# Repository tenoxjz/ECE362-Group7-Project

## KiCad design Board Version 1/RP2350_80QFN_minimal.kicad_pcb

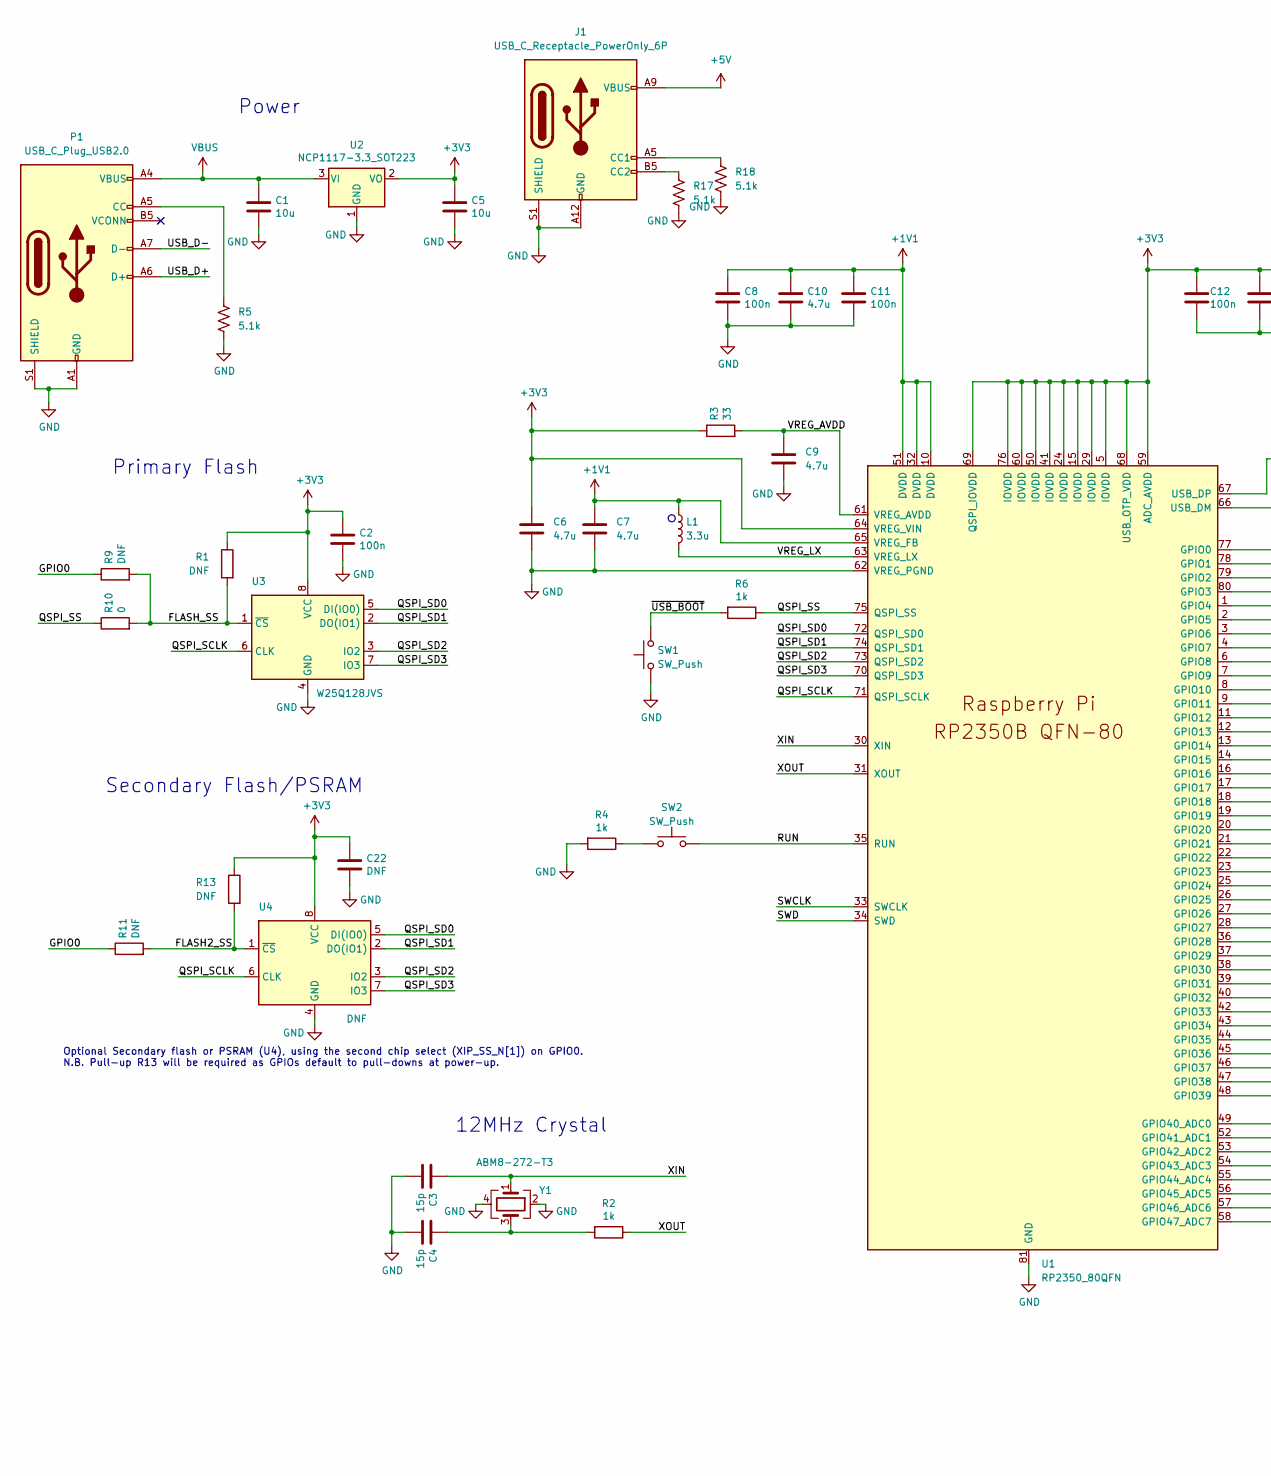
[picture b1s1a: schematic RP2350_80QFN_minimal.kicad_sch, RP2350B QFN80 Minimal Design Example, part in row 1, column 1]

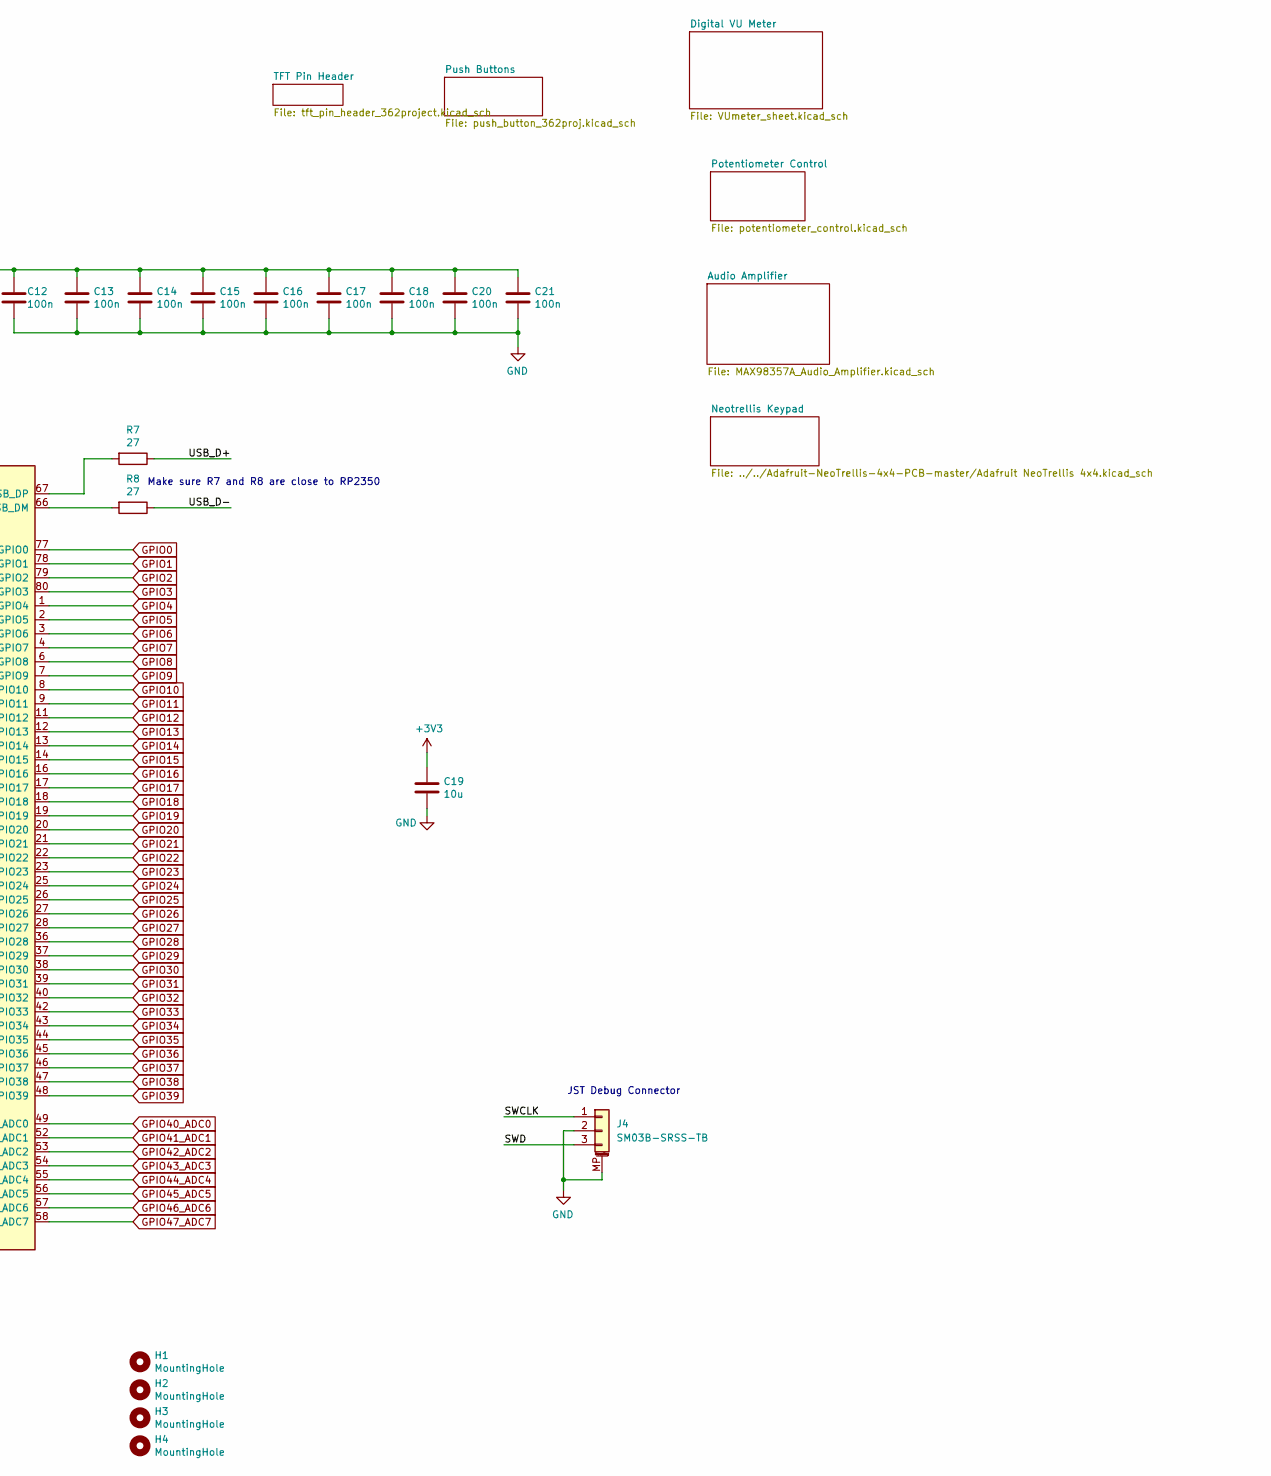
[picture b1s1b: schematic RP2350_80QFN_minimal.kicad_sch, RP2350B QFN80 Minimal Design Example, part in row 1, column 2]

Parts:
C1, C5, C19: 10u; C_0805_2012Metric
C2, C8, C11, C12, C13, C14, C15, C16, C17, C18, C20, C21: 100n; C_0402_1005Metric
C3, C4: 15p; C_0402_1005Metric
C6, C7: 4.7u; C_0402_1005Metric_small_pads
C9, C10: 4.7u; C_0402_1005Metric
C22: DNF; C_0402_1005Metric
H1, H2, H3, H4: MountingHole; MountingHole_2.7mm_M2.5
J1: USB_C_Receptacle_PowerOnly_6P; USB_C_Receptacle_GCT_USB4125-xx-x-0190_6P_TopMnt_Horizontal
J4: SM03B-SRSS-TB; JST_SH_SM03B-SRSS-TB_1x03-1MP_P1.00mm_Horizontal
L1: 3.3u; L_pol_2016
P1: USB_C_Plug_USB2.0; USB_C_Receptacle_HRO_TYPE-C-31-M-12
R1, R9, R11, R13: DNF; R_0402_1005Metric
R2, R4, R6: 1k; R_0402_1005Metric
R3: 33; R_0402_1005Metric
R5, R17, R18: 5.1k; R_0603_1608Metric
R7, R8: 27; R_0402_1005Metric
R10: 0; R_0402_1005Metric
SW1, SW2: SW_Push; SW_Push_1P1T_NO_Vertical_Wuerth_434133025816
U1: RP2350_80QFN; RP2350-QFN-80-1EP_10x10_P0.4mm_EP3.4x3.4mm_ThermalVias
U2: NCP1117-3.3_SOT223; SOT-223-3_TabPin2
U3: W25Q128JVS; SOIC-8_5.23x5.23mm_P1.27mm
U4: DNF; SOIC-8_5.23x5.23mm_P1.27mm
Y1: ABM8-272-T3; Crystal_SMD_3225-4Pin_3.2x2.5mm

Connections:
+1V1: C7.1, C8.1, C10.1, C11.1, L1.1, U1.10 (DVDD), U1.32 (DVDD), U1.51 (DVDD), U1.65 (VREG_FB)
+5V: J1.A9 (VBUS), J1.B9 (VBUS); also elsewhere on the board
/FLASH2_SS: R11.2, R13.2, U4.1 (~CS)
/FLASH_SS: R1.2, R9.2, R10.2, U3.1 (~CS)
/QSPI_SCLK: U1.71 (QSPI_SCLK), U3.6 (CLK), U4.6 (CLK)
/QSPI_SD0: U1.72 (QSPI_SD0), U3.5 (DI(IO0)), U4.5 (DI(IO0))
/QSPI_SD1: U1.74 (QSPI_SD1), U3.2 (DO(IO1)), U4.2 (DO(IO1))
/QSPI_SD2: U1.73 (QSPI_SD2), U3.3 (IO2), U4.3 (IO2)
/QSPI_SD3: U1.70 (QSPI_SD3), U3.7 (IO3), U4.7 (IO3)
/QSPI_SS: R6.1, R10.1, U1.75 (QSPI_SS)
/RUN: SW2.2, U1.35 (RUN)
/SWCLK: J4.1, U1.33 (SWCLK)
/SWD: J4.3, U1.34 (SWD)
/USB_D+: P1.A6 (D+), R7.1
/USB_D-: P1.A7 (D-), R8.1
/VREG_AVDD: C9.1, R3.2, U1.61 (VREG_AVDD)
/VREG_LX: L1.2, U1.63 (VREG_LX)
/XIN: C3.1, U1.30 (XIN), Y1.1
/XOUT: R2.1, U1.31 (XOUT)
/~USB_BOOT: R6.2, SW1.2
GND: C1.2, C2.2, C3.2, C4.2, C5.2, C6.2, C7.2, C8.2, C9.2, C10.2, C11.2, C12.2, C13.2, C14.2, C15.2, C16.2, C17.2, C18.2, C19.2, C20.2, C21.2, C22.2, J1.A12 (GND), J1.B12 (GND), J1.S1 (SHIELD), J4.2, J4.MP (MountPin), P1.A1 (GND), P1.A12 (GND), P1.B1 (GND), P1.B12 (GND), P1.S1 (SHIELD), R4.2, R5.2, R17.2, R18.2, SW1.1, U1.62 (VREG_PGND), U1.81 (GND), U2.1 (GND), U3.4 (GND), U4.4 (GND), Y1.2, Y1.4; also elsewhere on the board
GPIO0: R9.1, R11.1, U1.77 (GPIO0)
GPIO1: U1.78 (GPIO1)
GPIO2: U1.79 (GPIO2)
GPIO3: U1.80 (GPIO3); also elsewhere on the board
GPIO4: U1.1 (GPIO4); also elsewhere on the board
GPIO5: U1.2 (GPIO5); also elsewhere on the board
GPIO6: U1.3 (GPIO6); also elsewhere on the board
GPIO7: U1.4 (GPIO7); also elsewhere on the board
GPIO8: U1.6 (GPIO8)
GPIO9: U1.7 (GPIO9)
GPIO10: U1.8 (GPIO10)
GPIO11: U1.9 (GPIO11)
GPIO12: U1.11 (GPIO12)
GPIO13: U1.12 (GPIO13)
GPIO14: U1.13 (GPIO14)
GPIO15: U1.14 (GPIO15)
GPIO16: U1.16 (GPIO16); also elsewhere on the board
GPIO17: U1.17 (GPIO17); also elsewhere on the board
GPIO18: U1.18 (GPIO18); also elsewhere on the board
GPIO19: U1.19 (GPIO19); also elsewhere on the board
GPIO20: U1.20 (GPIO20); also elsewhere on the board
GPIO21: U1.21 (GPIO21)
GPIO22: U1.22 (GPIO22)
GPIO23: U1.23 (GPIO23)
GPIO24: U1.25 (GPIO24); also elsewhere on the board
GPIO25: U1.26 (GPIO25); also elsewhere on the board
GPIO26: U1.27 (GPIO26)
GPIO27: U1.28 (GPIO27)
GPIO28: U1.36 (GPIO28)
GPIO29: U1.37 (GPIO29); also elsewhere on the board
GPIO30: U1.38 (GPIO30); also elsewhere on the board
GPIO31: U1.39 (GPIO31); also elsewhere on the board
GPIO32: U1.40 (GPIO32)
GPIO33: U1.42 (GPIO33)
GPIO34: U1.43 (GPIO34)
GPIO35: U1.44 (GPIO35)
GPIO36: U1.45 (GPIO36); also elsewhere on the board
GPIO37: U1.46 (GPIO37); also elsewhere on the board
GPIO38: U1.47 (GPIO38); also elsewhere on the board
GPIO39: U1.48 (GPIO39); also elsewhere on the board
GPIO40_ADC0: U1.49 (GPIO40_ADC0)
GPIO41_ADC1: U1.52 (GPIO41_ADC1)
GPIO42_ADC2: U1.53 (GPIO42_ADC2)
GPIO43_ADC3: U1.54 (GPIO43_ADC3); also elsewhere on the board
GPIO44_ADC4: U1.55 (GPIO44_ADC4)
GPIO45_ADC5: U1.56 (GPIO45_ADC5); also elsewhere on the board
GPIO46_ADC6: U1.57 (GPIO46_ADC6)
GPIO47_ADC7: U1.58 (GPIO47_ADC7); also elsewhere on the board
unnamed: C4.1, R2.2, Y1.3
unnamed: J1.A5 (CC1), R18.1
unnamed: J1.B5 (CC2), R17.1
unnamed: P1.A5 (CC), R5.1
unnamed: R4.1, SW2.1
unnamed: R8.2, U1.66 (USB_DM)
unnamed: R7.2, U1.67 (USB_DP)
VBUS: C1.1, P1.A4 (VBUS), P1.A9 (VBUS), P1.B4 (VBUS), P1.B9 (VBUS), U2.3 (VI)

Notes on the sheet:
Optional Secondary flash or PSRAM (U4), using the second chip select (XIP_SS_N[1]) on GPIO0. N.B. Pull-up R13 will be required as GPIOs default to pull-downs at power-up.
12MHz Crystal
Primary Flash
JST Debug Connector
Make sure R7 and R8 are close to RP2350
Secondary Flash/PSRAM
Power

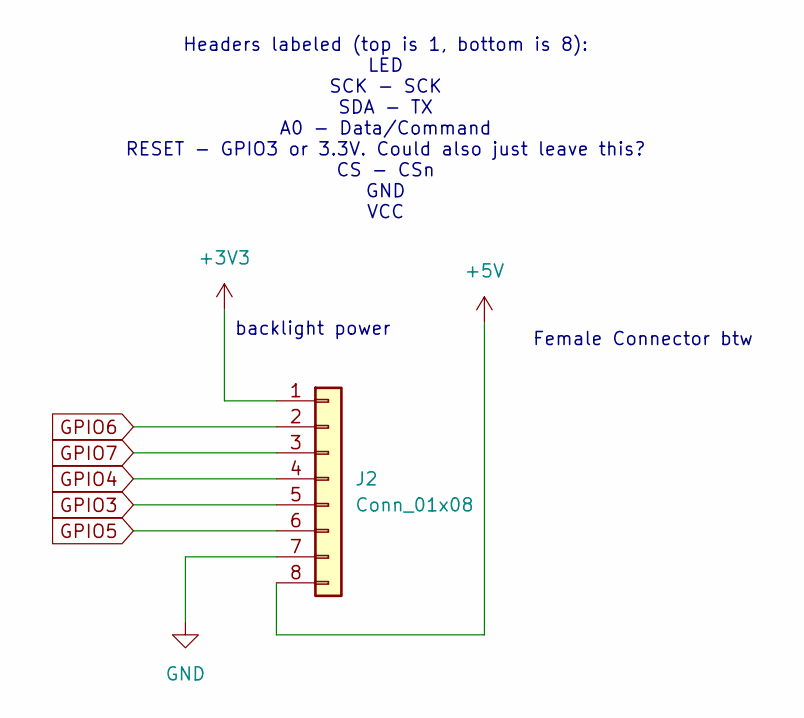
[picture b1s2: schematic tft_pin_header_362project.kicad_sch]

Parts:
J2: Conn_01x08; PinHeader_1x08_P2.54mm_Vertical

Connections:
+5V: J2.8; also elsewhere on the board
GND: J2.7; also elsewhere on the board
GPIO3: J2.5; also elsewhere on the board
GPIO4: J2.4; also elsewhere on the board
GPIO5: J2.6; also elsewhere on the board
GPIO6: J2.2; also elsewhere on the board
GPIO7: J2.3; also elsewhere on the board

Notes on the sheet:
Headers labeled (top is 1, bottom is 8): LED SCK - SCK SDA - TX A0 - Data/Command RESET - GPIO3 or 3.3V. Could also just leave this? CS - CSn GND VCC
backlight power
Female Connector btw

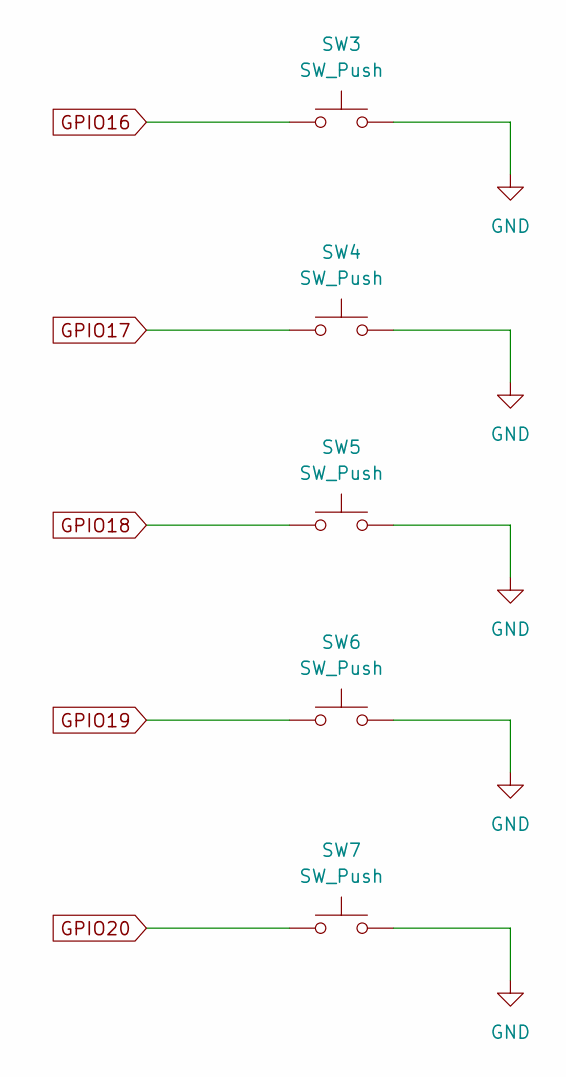
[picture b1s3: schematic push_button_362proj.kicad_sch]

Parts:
SW3, SW4, SW5, SW6, SW7: SW_Push; SW_Push_1P1T_NO_Vertical_Wuerth_434133025816

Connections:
GND: SW3.2, SW4.2, SW5.2, SW6.2, SW7.2; also elsewhere on the board
GPIO16: SW3.1; also elsewhere on the board
GPIO17: SW4.1; also elsewhere on the board
GPIO18: SW5.1; also elsewhere on the board
GPIO19: SW6.1; also elsewhere on the board
GPIO20: SW7.1; also elsewhere on the board

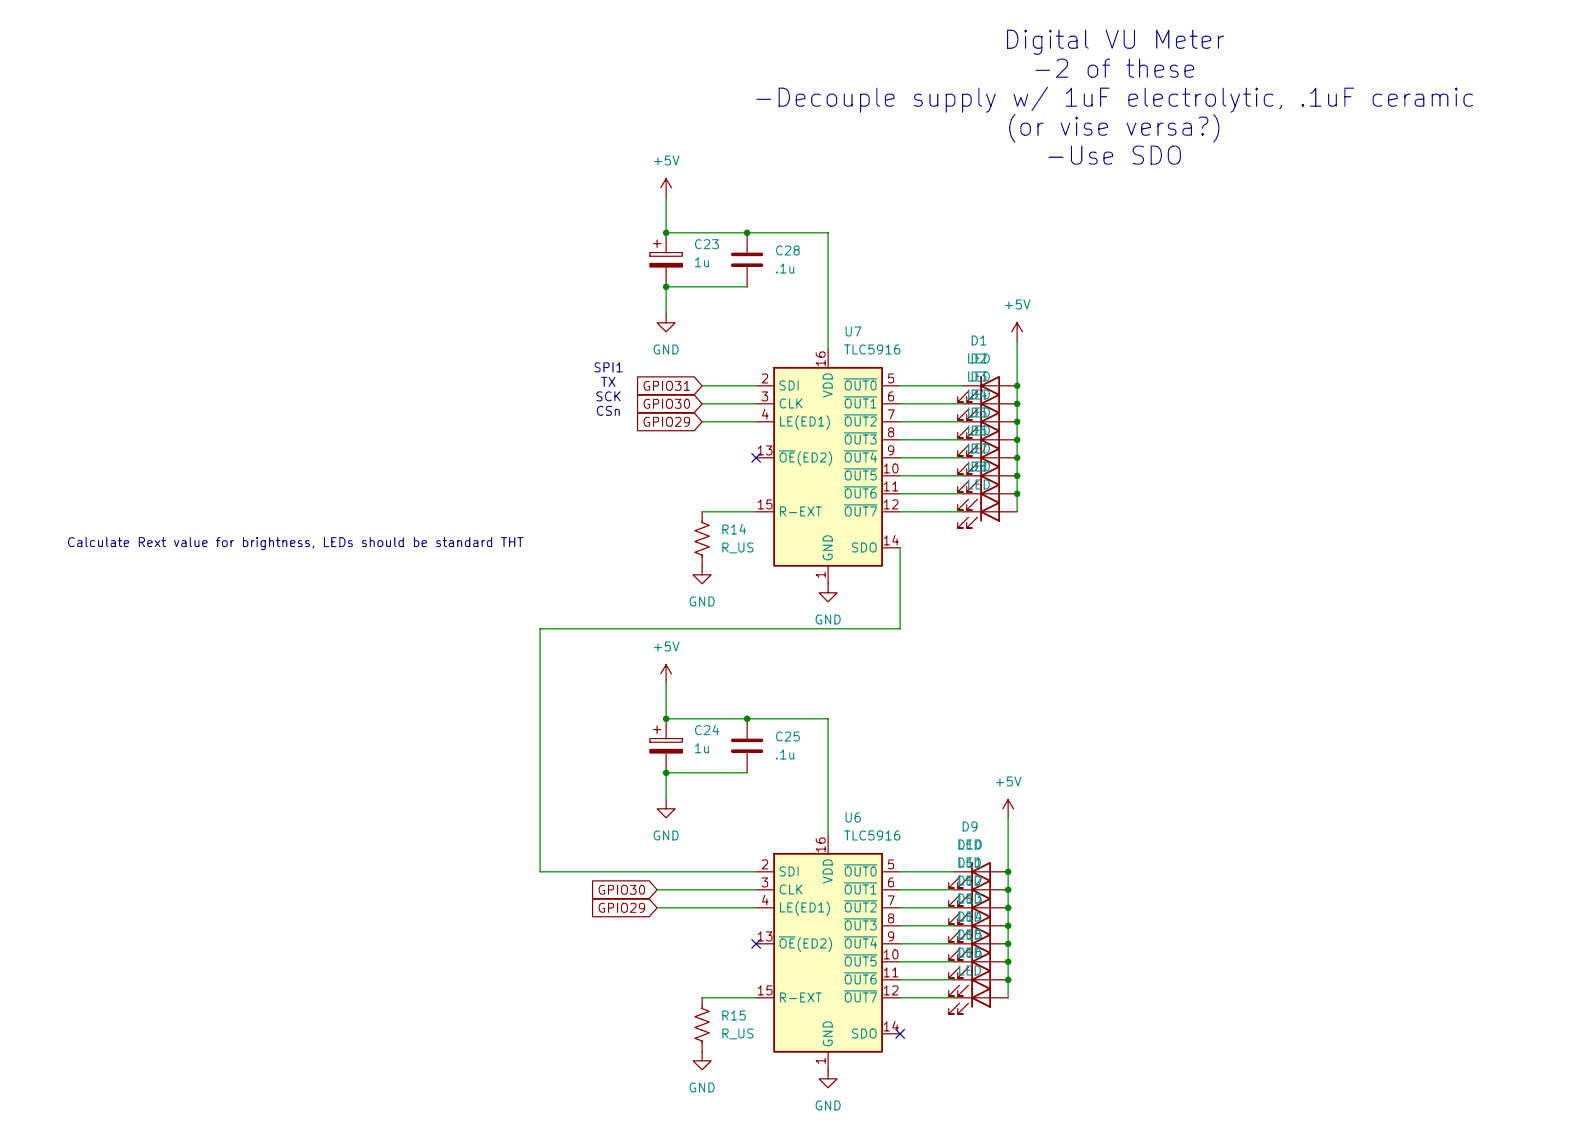
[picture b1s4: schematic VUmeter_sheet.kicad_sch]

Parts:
C23, C24: 1u; C_0805_2012Metric
C25, C28: .1u; C_0402_1005Metric
D1, D2, D3, D4, D5, D6, D7, D8, D9, D10, D11, D12, D13, D14, D15, D16: LED; LED_D3.0mm
R14, R15: R_US; R_0603_1608Metric
U6, U7: TLC5916; DIP-16_W7.62mm

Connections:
+5V: C23.1, C24.1, C25.1, C28.1, D1.2 (A), D2.2 (A), D3.2 (A), D4.2 (A), D5.2 (A), D6.2 (A), D7.2 (A), D8.2 (A), D9.2 (A), D10.2 (A), D11.2 (A), D12.2 (A), D13.2 (A), D14.2 (A), D15.2 (A), D16.2 (A), U6.16 (VDD), U7.16 (VDD); also elsewhere on the board
GND: C23.2, C24.2, C25.2, C28.2, R14.2, R15.2, U6.1 (GND), U7.1 (GND); also elsewhere on the board
GPIO29: U6.4 (LE(ED1)), U7.4 (LE(ED1)); also elsewhere on the board
GPIO30: U6.3 (CLK), U7.3 (CLK); also elsewhere on the board
GPIO31: U7.2 (SDI); also elsewhere on the board
unnamed: D1.1 (K), U7.5 (~OUT0)
unnamed: D2.1 (K), U7.6 (~OUT1)
unnamed: D3.1 (K), U7.7 (~OUT2)
unnamed: D4.1 (K), U7.8 (~OUT3)
unnamed: D5.1 (K), U7.9 (~OUT4)
unnamed: D6.1 (K), U7.10 (~OUT5)
unnamed: D7.1 (K), U7.11 (~OUT6)
unnamed: D8.1 (K), U7.12 (~OUT7)
unnamed: D9.1 (K), U6.5 (~OUT0)
unnamed: D10.1 (K), U6.6 (~OUT1)
unnamed: D11.1 (K), U6.7 (~OUT2)
unnamed: D12.1 (K), U6.8 (~OUT3)
unnamed: D13.1 (K), U6.9 (~OUT4)
unnamed: D14.1 (K), U6.10 (~OUT5)
unnamed: D15.1 (K), U6.11 (~OUT6)
unnamed: D16.1 (K), U6.12 (~OUT7)
unnamed: R15.1, U6.15 (R-EXT)
unnamed: U6.2 (SDI), U7.14 (SDO)
unnamed: R14.1, U7.15 (R-EXT)

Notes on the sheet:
SPI1 TX SCK CSn
Calculate Rext value for brightness, LEDs should be standard THT
Digital VU Meter -2 of these -Decouple supply w/ 1uF electrolytic, .1uF ceramic (or vise versa?) -Use SDO

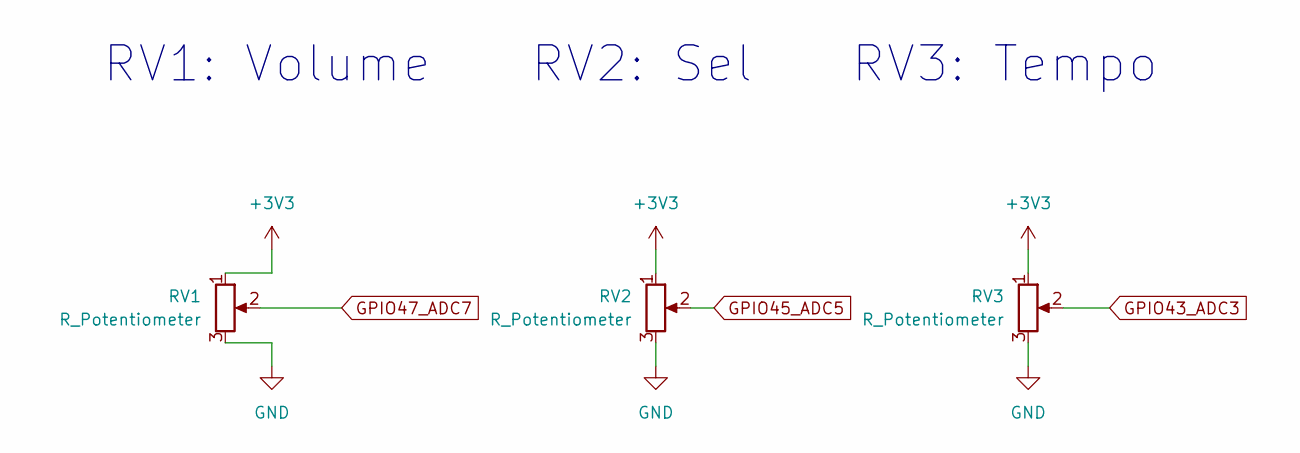
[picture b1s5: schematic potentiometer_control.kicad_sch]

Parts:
RV1, RV2, RV3: R_Potentiometer; Potentiometer_Bourns_3266Y_Vertical

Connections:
GND: RV1.3, RV2.3, RV3.3; also elsewhere on the board
GPIO43_ADC3: RV3.2; also elsewhere on the board
GPIO45_ADC5: RV2.2; also elsewhere on the board
GPIO47_ADC7: RV1.2; also elsewhere on the board

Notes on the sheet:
RV3: Tempo
RV2: Sel
RV1: Volume

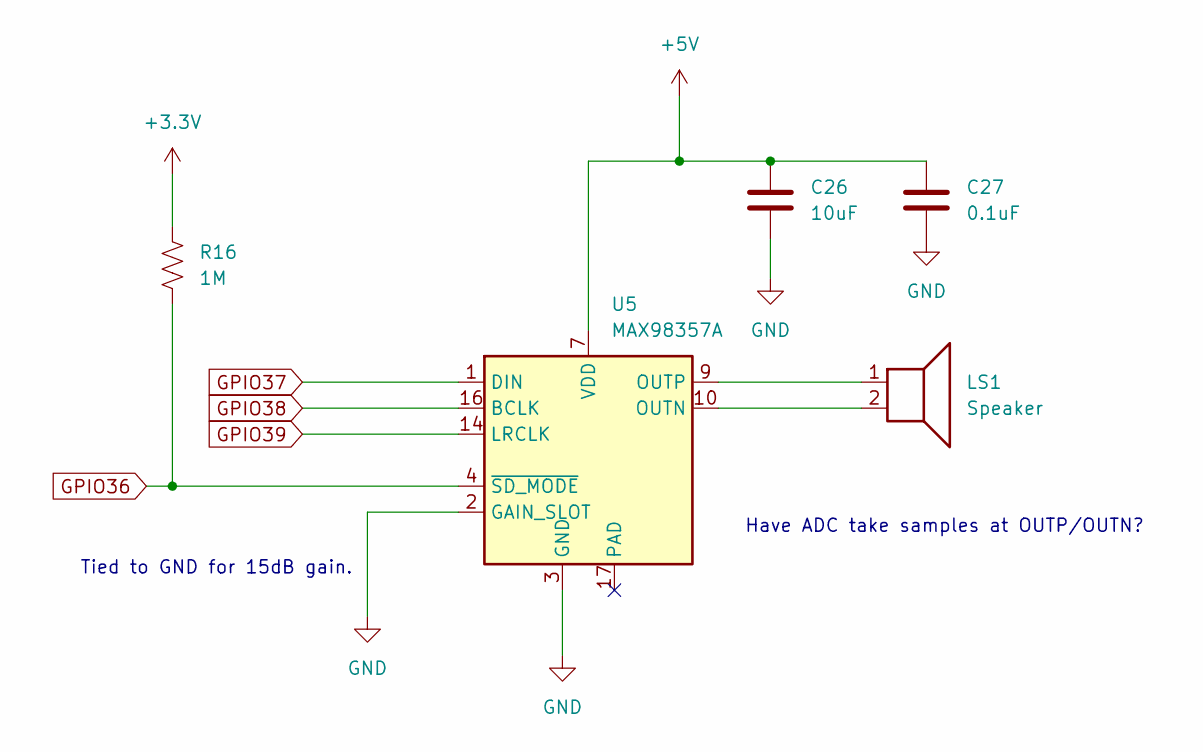
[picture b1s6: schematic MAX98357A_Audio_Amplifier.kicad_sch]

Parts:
C26: 10uF; C_0805_2012Metric
C27: 0.1uF; C_0805_2012Metric
LS1: Speaker; PinHeader_1x02_P2.54mm_Vertical
R16: 1M; R_0805_2012Metric
U5: MAX98357A; TQFN-16-1EP_3x3mm_P0.5mm_EP1.23x1.23mm

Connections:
+5V: C26.1, C27.1, U5.7 (VDD), U5.8 (VDD); also elsewhere on the board
GND: C26.2, C27.2, U5.2 (GAIN_SLOT), U5.3 (GND), U5.11 (GND), U5.15 (GND); also elsewhere on the board
GPIO36: R16.2, U5.4 (~SD_MODE); also elsewhere on the board
GPIO37: U5.1 (DIN); also elsewhere on the board
GPIO38: U5.16 (BCLK); also elsewhere on the board
GPIO39: U5.14 (LRCLK); also elsewhere on the board
unnamed: LS1.2, U5.10 (OUTN)
unnamed: LS1.1, U5.9 (OUTP)

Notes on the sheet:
Have ADC take samples at OUTP/OUTN?
Tied to GND for 15dB gain.

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
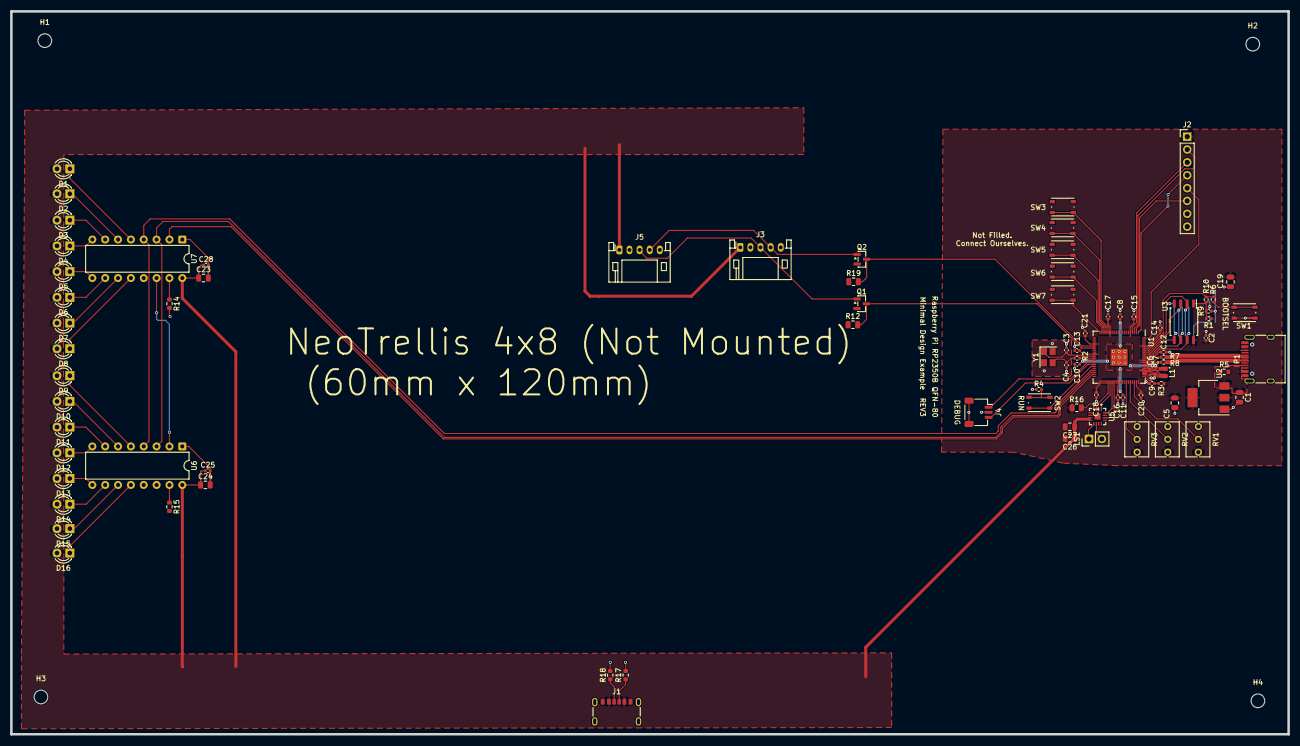
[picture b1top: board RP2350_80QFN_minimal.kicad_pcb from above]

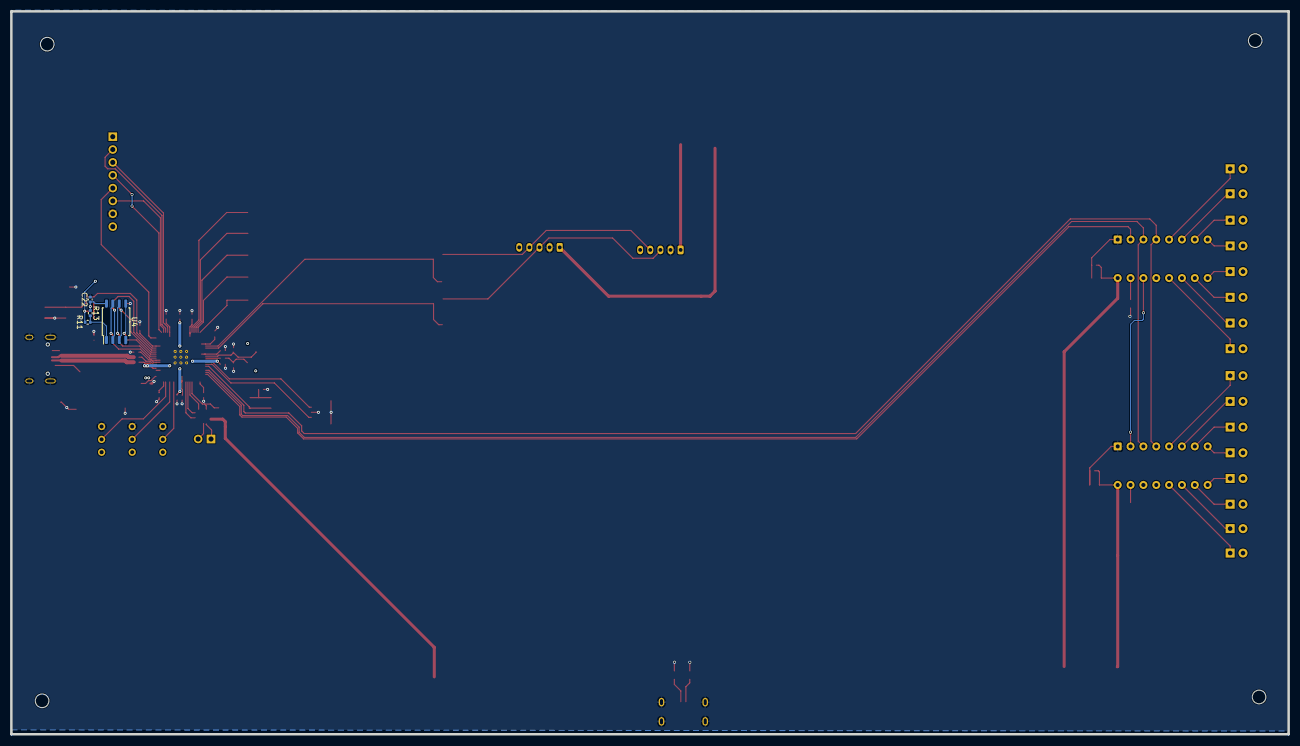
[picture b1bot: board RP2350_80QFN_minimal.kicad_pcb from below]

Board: 2 copper layers, 252.5 x 142.9 mm, 95 parts (4 on the bottom side), 76 nets.

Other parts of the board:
J3, J5: Conn_01x04; JST_PH_S5B-PH-K_1x05_P2.00mm_Horizontal
Q1, Q2: NMOS; SOT-23
R12, R19: 10k; C_0805_2012Metric

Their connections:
+5V: J3.1, J5.1; also elsewhere on the board
GND: J3.2, J5.2; also elsewhere on the board
GPIO24: Q2.3 (S), R19.2; also elsewhere on the board
GPIO25: Q1.3 (S), R12.2; also elsewhere on the board
unnamed: J3.3, J5.3, Q1.1 (D)
unnamed: J3.4, J5.4, Q2.1 (D)

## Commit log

2026-03-05 Base Schematic
    Schematic from the Hardware guide w/o footprint assignments, GPIO pin headers, and all of our chosen peripherals implemented. Also has USB_B_Micro and JST, this can be changed to the USB-C version.
2026-03-27 Board Version 1
    Completed layout for all parts, BOM not done.
